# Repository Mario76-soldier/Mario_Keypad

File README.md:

# Mario_Keypad
This is applicated keypad such as ctrl+c and ctrl+v

## Cloning

This repository uses a git submodule for the key switch footprint library. Clone with:

```sh
git clone --recurse-submodules <this-repo-url>
```

If you already cloned without it:

```sh
git submodule update --init
```

## License

This repository contains code and design files under several licenses.
Each third-party component keeps its own license; the MIT license in [LICENSE](LICENSE) covers only this project's own work.

| Path | License | Copyright / Source |
|---|---|---|
| `Core/`, `USB_DEVICE/`, `STM32F103C8TX_FLASH.ld`, `Keypad.ioc` | [MIT](LICENSE) | © 2026 Mario76-soldier. Includes code generated by STM32CubeMX (© STMicroelectronics). Those files say they follow the LICENSE file in the root directory. |
| `Keypad_PCB/`, `LED.pretty/` | [MIT](LICENSE) | © 2026 Mario76-soldier. The PCB includes footprints from `keyswitches.pretty`, which stay under CC BY-SA 4.0 (see below). |
| `keyswitches.pretty/` (git submodule) | [CC BY-SA 4.0](https://creativecommons.org/licenses/by-sa/4.0/) | © daprice and contributors: <https://github.com/daprice/keyswitches.pretty> |
| `Drivers/STM32F1xx_HAL_Driver/` | [BSD-3-Clause](Drivers/STM32F1xx_HAL_Driver/LICENSE.txt) | © STMicroelectronics |
| `Drivers/CMSIS/Device/ST/` | [Apache-2.0](Drivers/CMSIS/Device/ST/STM32F1xx/LICENSE.txt) | © STMicroelectronics |
| `Drivers/CMSIS/` (Core) | [Apache-2.0](Drivers/CMSIS/LICENSE.txt) | © Arm Limited |
| `Middlewares/ST/STM32_USB_Device_Library/` | [ST Ultimate Liberty License SLA0044](https://www.st.com/SLA0044) | © STMicroelectronics |

### Third-party notices

- **keyswitches.pretty**: Mechanical keyboard switch footprints for KiCad by daprice, licensed under [Creative Commons Attribution-ShareAlike 4.0 International](https://creativecommons.org/licenses/by-sa/4.0/). If you modify and distribute these footprints, you must share them under the same license.
- **STM32Cube HAL / CMSIS / USB Device Library**: Provided by STMicroelectronics and Arm. The USB Device Library (SLA0044) may only be used on STMicroelectronics microcontrollers. See the license headers in each source file.

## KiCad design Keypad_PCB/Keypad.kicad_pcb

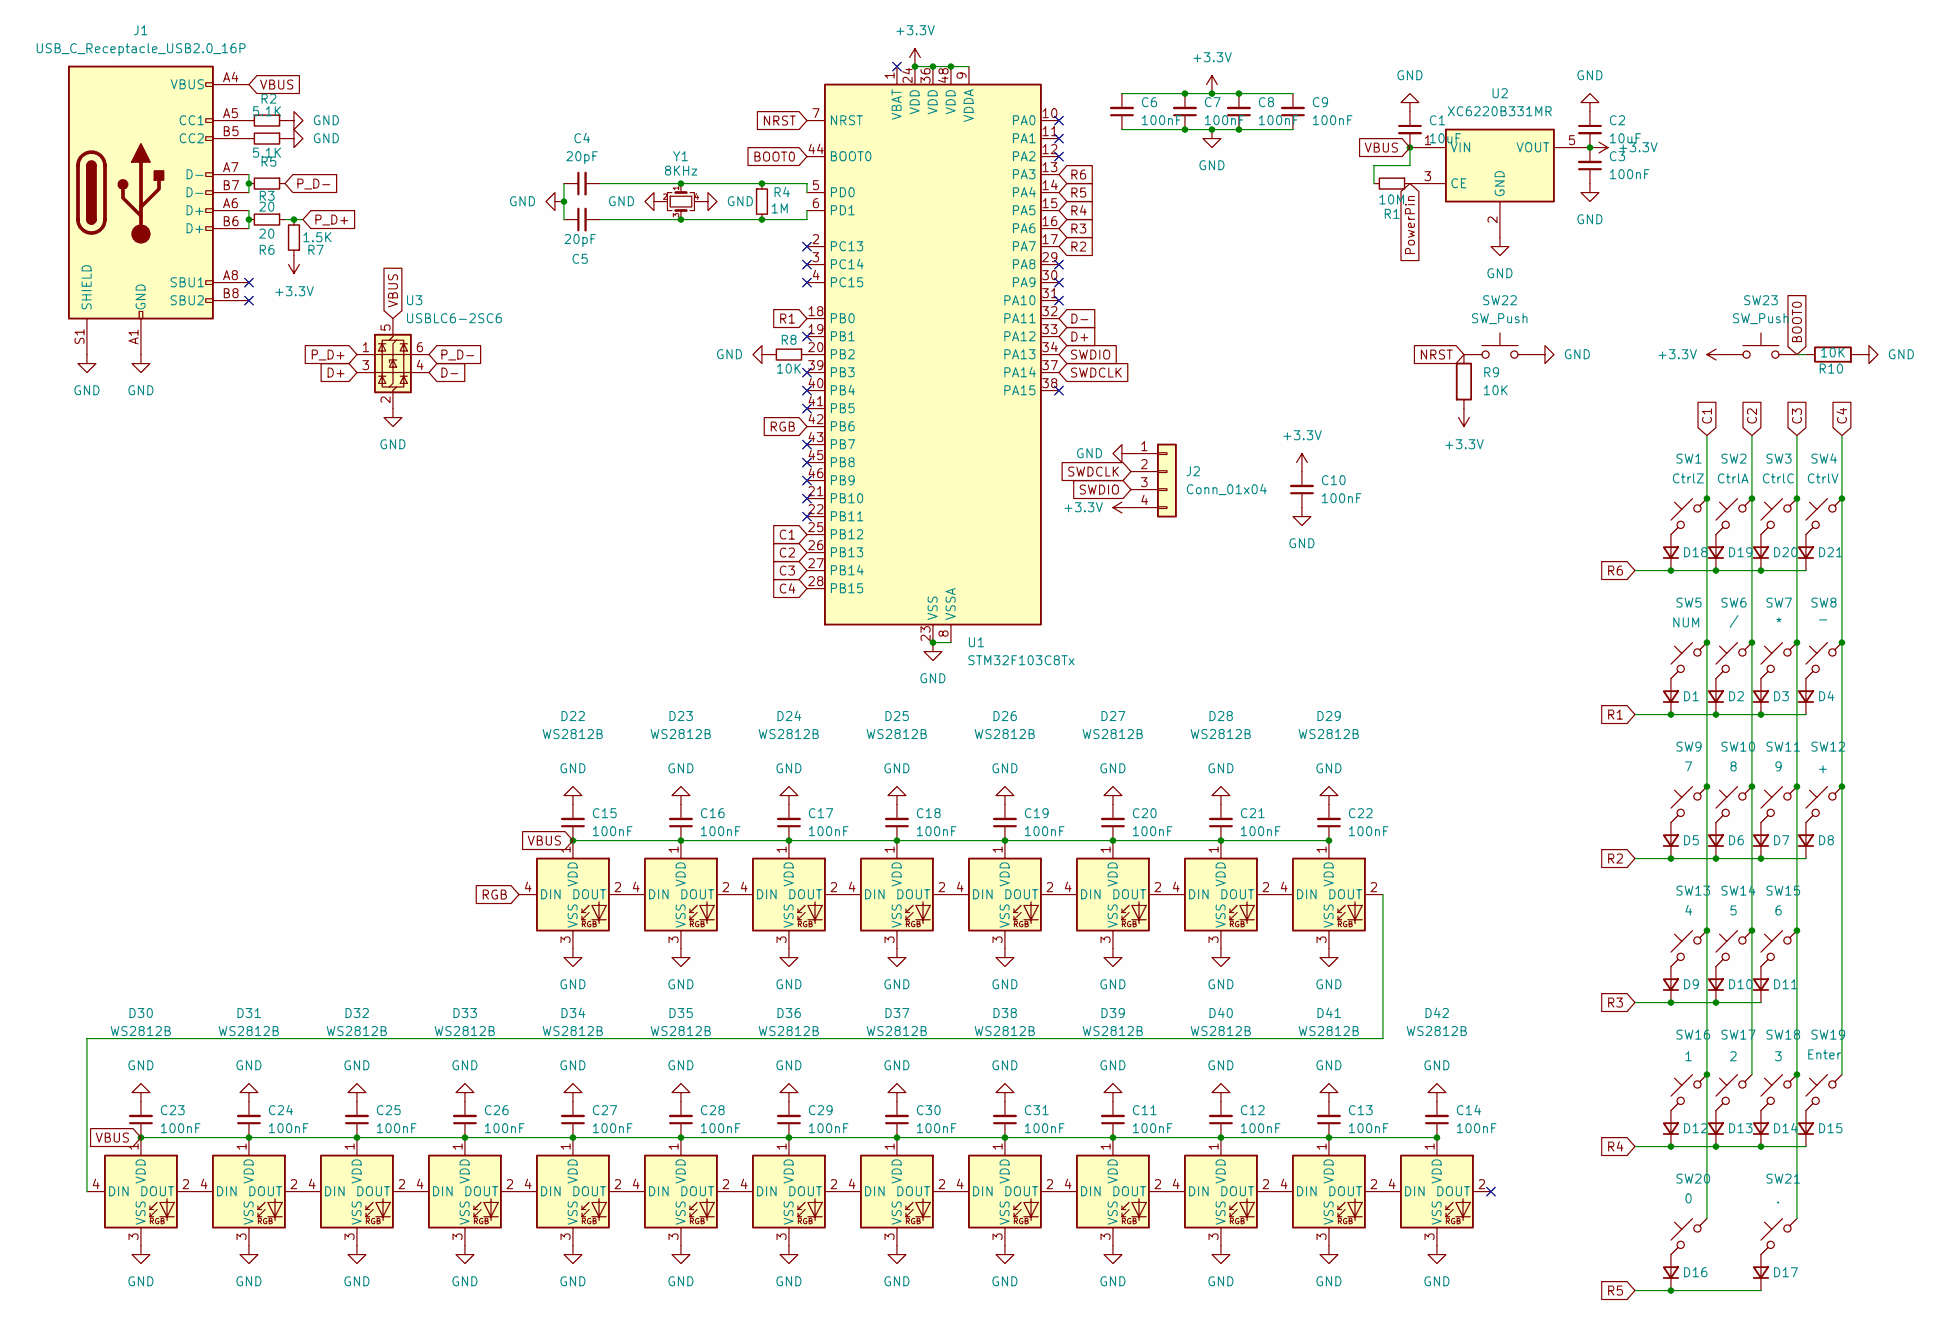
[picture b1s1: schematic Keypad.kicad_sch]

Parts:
C1, C2: 10uF; C_0603_1608Metric
C3, C6, C7, C8, C9, C10, C11, C12, C13, C14, C15, C16, C17, C18, C19, C20, C21, C22, C23, C24, C25, C26, C27, C28, C29, C30, C31: 100nF; C_0603_1608Metric
C4, C5: 20pF; C_0603_1608Metric
D1, D2, D3, D4, D5, D6, D7, D8, D9, D10, D11, D12, D13, D14, D15, D16, D17, D18, D19, D20, D21: D_Small; D_SOD-123
D22, D23, D24, D25, D26, D27, D28, D29, D30, D31, D32, D33, D34, D35, D36, D37, D38, D39, D40, D41, D42: WS2812B; WS2812_6028
J1: USB_C_Receptacle_USB2.0_16P; USB_C_Receptacle_HCTL_HC-TYPE-C-16P-01A
J2: Conn_01x04; PinHeader_1x04_P2.54mm_Vertical
R1: 10M; R_0603_1608Metric
R2, R3: 5.1K; R_0603_1608Metric
R4: 1M; R_0603_1608Metric
R5, R6: 20; R_0603_1608Metric
R7: 1.5K; R_0603_1608Metric
R8, R9, R10: 10K; R_0603_1608Metric
SW1: CtrlZ; Kailh_socket_MX
SW2: CtrlA; Kailh_socket_MX
SW3: CtrlC; Kailh_socket_MX
SW4: CtrlV; Kailh_socket_MX
SW5: NUM; Kailh_socket_MX
SW6: /; Kailh_socket_MX
SW7: *; Kailh_socket_MX
SW8: -; Kailh_socket_MX
SW9: 7; Kailh_socket_MX
SW10: 8; Kailh_socket_MX
SW11: 9; Kailh_socket_MX
SW12: +; Kailh_socket_MX
SW13: 4; Kailh_socket_MX
SW14: 5; Kailh_socket_MX
SW15: 6; Kailh_socket_MX
SW16: 1; Kailh_socket_MX
SW17: 2; Kailh_socket_MX
SW18: 3; Kailh_socket_MX
SW19: Enter; Kailh_socket_MX
SW20: 0; Kailh_socket_MX
SW21: .; Kailh_socket_MX
SW22, SW23: SW_Push; SW_Push_SPST_NO_Alps_SKRK
U1: STM32F103C8Tx; LQFP-48_7x7mm_P0.5mm
U2: XC6220B331MR; SOT-23-5
U3: USBLC6-2SC6; SOT-23-6
Y1: 8KHz; Crystal_SMD_3225-4Pin_3.2x2.5mm

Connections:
BOOT0: R10.1, SW23.2, U1.44 (BOOT0)
C1: SW1.2, SW5.2, SW9.2, SW13.2, SW16.2, SW20.2, U1.25 (PB12)
C2: SW2.2, SW6.2, SW10.2, SW14.2, SW17.2, U1.26 (PB13)
C3: SW3.2, SW7.2, SW11.2, SW15.2, SW18.2, SW21.2, U1.27 (PB14)
C4: SW4.2, SW8.2, SW12.2, SW19.2, U1.28 (PB15)
D+: U1.33 (PA12), U3.3 (I/O2)
D-: U1.32 (PA11), U3.4 (I/O2)
GND: C1.1, C2.1, C3.1, C4.1, C5.1, C6.1, C7.1, C8.1, C9.1, C10.1, C11.2, C12.2, C13.2, C14.2, C15.2, C16.2, C17.2, C18.2, C19.2, C20.2, C21.2, C22.2, C23.2, C24.2, C25.2, C26.2, C27.2, C28.2, C29.2, C30.2, C31.2, D22.3 (VSS), D23.3 (VSS), D24.3 (VSS), D25.3 (VSS), D26.3 (VSS), D27.3 (VSS), D28.3 (VSS), D29.3 (VSS), D30.3 (VSS), D31.3 (VSS), D32.3 (VSS), D33.3 (VSS), D34.3 (VSS), D35.3 (VSS), D36.3 (VSS), D37.3 (VSS), D38.3 (VSS), D39.3 (VSS), D40.3 (VSS), D41.3 (VSS), D42.3 (VSS), J1.A1 (GND), J1.A12 (GND), J1.B1 (GND), J1.B12 (GND), J1.S1 (SHIELD), J2.1, R2.1, R3.1, R8.2, R10.2, SW22.2, U1.8 (VSSA), U1.23 (VSS), U1.35 (VSS), U1.47 (VSS), U2.2 (GND), U3.2 (GND), Y1.2, Y1.4
NRST: R9.1, SW22.1, U1.7 (NRST)
unnamed: D1.2 (A), SW5.1
unnamed: D2.2 (A), SW6.1
unnamed: D3.2 (A), SW7.1
unnamed: D4.2 (A), SW8.1
unnamed: D5.2 (A), SW9.1
unnamed: D6.2 (A), SW10.1
unnamed: D7.2 (A), SW11.1
unnamed: D8.2 (A), SW12.1
unnamed: D9.2 (A), SW13.1
unnamed: D10.2 (A), SW14.1
unnamed: D11.2 (A), SW15.1
unnamed: D12.2 (A), SW16.1
unnamed: D13.2 (A), SW17.1
unnamed: D14.2 (A), SW18.1
unnamed: D15.2 (A), SW19.1
unnamed: D16.2 (A), SW20.1
unnamed: D17.2 (A), SW21.1
unnamed: D18.2 (A), SW1.1
unnamed: D19.2 (A), SW2.1
unnamed: D20.2 (A), SW3.1
unnamed: D21.2 (A), SW4.1
unnamed: D22.2 (DOUT), D23.4 (DIN)
unnamed: D23.2 (DOUT), D24.4 (DIN)
unnamed: D24.2 (DOUT), D25.4 (DIN)
unnamed: D25.2 (DOUT), D26.4 (DIN)
unnamed: D26.2 (DOUT), D27.4 (DIN)
unnamed: D27.2 (DOUT), D28.4 (DIN)
unnamed: D28.2 (DOUT), D29.4 (DIN)
unnamed: D29.2 (DOUT), D30.4 (DIN)
unnamed: D30.2 (DOUT), D31.4 (DIN)
unnamed: D31.2 (DOUT), D32.4 (DIN)
unnamed: D32.2 (DOUT), D33.4 (DIN)
unnamed: D33.2 (DOUT), D34.4 (DIN)
unnamed: D34.2 (DOUT), D35.4 (DIN)
unnamed: D35.2 (DOUT), D36.4 (DIN)
unnamed: D36.2 (DOUT), D37.4 (DIN)
unnamed: D37.2 (DOUT), D38.4 (DIN)
unnamed: D38.2 (DOUT), D39.4 (DIN)
unnamed: D39.2 (DOUT), D40.4 (DIN)
unnamed: D40.2 (DOUT), D41.4 (DIN)
unnamed: D41.2 (DOUT), D42.4 (DIN)
unnamed: J1.A5 (CC1), R2.2
unnamed: J1.B5 (CC2), R3.2
unnamed: J1.A6 (D+), J1.B6 (D+), R6.2
unnamed: J1.A7 (D-), J1.B7 (D-), R5.2
unnamed: R8.1, U1.20 (PB2)
unnamed: C4.2, R4.1, U1.5 (PD0), Y1.1
unnamed: C5.2, R4.2, U1.6 (PD1), Y1.3
P_D+: R6.1, R7.2, U3.1 (I/O1)
P_D-: R5.1, U3.6 (I/O1)
PowerPin: R1.1, U2.3 (CE)
R1: D1.1 (K), D2.1 (K), D3.1 (K), D4.1 (K), U1.18 (PB0)
R2: D5.1 (K), D6.1 (K), D7.1 (K), D8.1 (K), U1.17 (PA7)
R3: D9.1 (K), D10.1 (K), D11.1 (K), U1.16 (PA6)
R4: D12.1 (K), D13.1 (K), D14.1 (K), D15.1 (K), U1.15 (PA5)
R5: D16.1 (K), D17.1 (K), U1.14 (PA4)
R6: D18.1 (K), D19.1 (K), D20.1 (K), D21.1 (K), U1.13 (PA3)
RGB: D22.4 (DIN), U1.42 (PB6)
SWDCLK: J2.2, U1.37 (PA14)
SWDIO: J2.3, U1.34 (PA13)

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
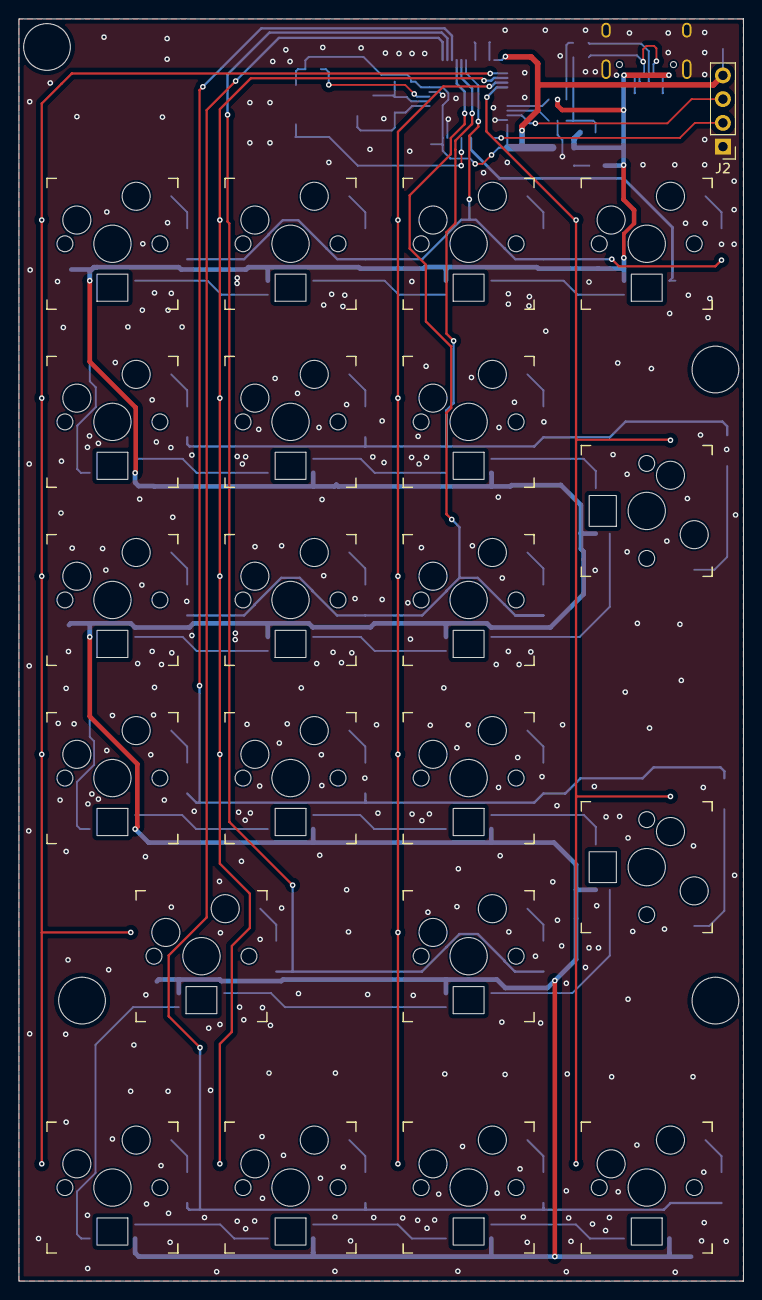
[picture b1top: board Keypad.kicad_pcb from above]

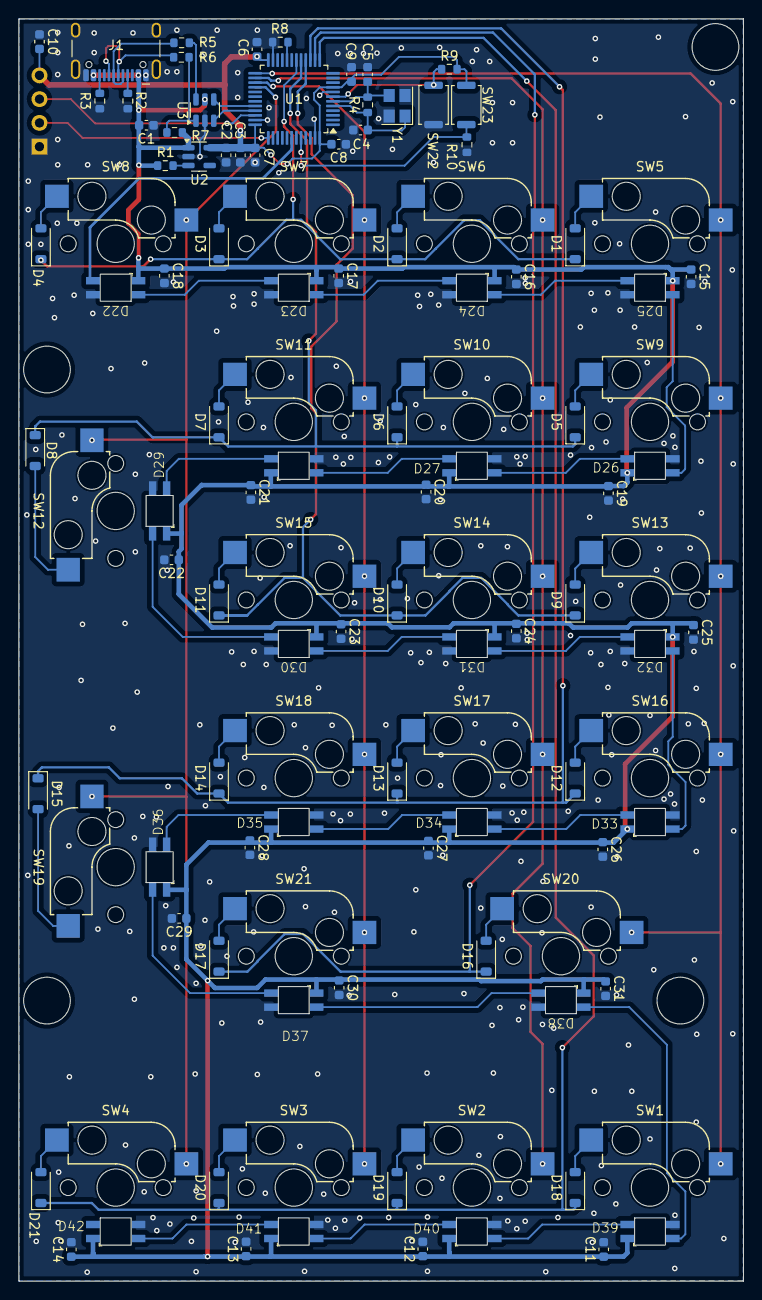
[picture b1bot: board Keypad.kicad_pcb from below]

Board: 2 copper layers, 77.5 x 135.0 mm, 112 parts (90 on the bottom side), 71 nets.

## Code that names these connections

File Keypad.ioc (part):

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Mcu.Name=STM32F103C(8-B)Tx
Mcu.Package=LQFP48
Mcu.UserName=STM32F103C8Tx
PA11.Mode=Device
PA11.Signal=USB_DM
PA12.Mode=Device
PA12.Signal=USB_DP
PA13.Mode=Serial_Wire
PA13.Signal=SYS_JTMS-SWDIO
PA14.Mode=Serial_Wire
PA14.Signal=SYS_JTCK-SWCLK
PA3.GPIOParameters=GPIO_Label
PA3.GPIO_Label=R5
PA3.Signal=GPIO_Output
PA4.GPIOParameters=GPIO_Label
PA4.GPIO_Label=R4
PA4.Signal=GPIO_Output
PA5.GPIOParameters=GPIO_Label
PA5.GPIO_Label=R3
PA5.Signal=GPIO_Output
PA6.GPIOParameters=GPIO_Label
PA6.GPIO_Label=R2
PA6.Signal=GPIO_Output
PA7.GPIOParameters=GPIO_Label
PA7.GPIO_Label=R1
PA7.Signal=GPIO_Output
PB0.GPIOParameters=GPIO_Label
PB0.GPIO_Label=R0
PB0.Signal=GPIO_Output
PB12.GPIOParameters=GPIO_PuPd,GPIO_Label
PB12.GPIO_Label=C1
PB12.GPIO_PuPd=GPIO_PULLUP
PB12.Signal=GPIO_Input
PB13.GPIOParameters=GPIO_PuPd,GPIO_Label
PB13.GPIO_Label=C2
PB13.GPIO_PuPd=GPIO_PULLUP
PB13.Signal=GPIO_Input
PB14.GPIOParameters=GPIO_PuPd,GPIO_Label
PB14.GPIO_Label=C3
PB14.GPIO_PuPd=GPIO_PULLUP
PB14.Signal=GPIO_Input
PB15.GPIOParameters=GPIO_PuPd,GPIO_Label
PB15.GPIO_Label=C4
PB15.GPIO_PuPd=GPIO_PULLUP
PB15.Signal=GPIO_Input
PB6.Signal=S_TIM4_CH1
PD0-OSC_IN.Mode=HSE-External-Oscillator
PD0-OSC_IN.Signal=RCC_OSC_IN
PD1-OSC_OUT.Mode=HSE-External-Oscillator
PD1-OSC_OUT.Signal=RCC_OSC_OUT
RCC.SYSCLKFreq_VALUE=72000000
RCC.SYSCLKSource=RCC_SYSCLKSOURCE_PLLCLK
board=custom
